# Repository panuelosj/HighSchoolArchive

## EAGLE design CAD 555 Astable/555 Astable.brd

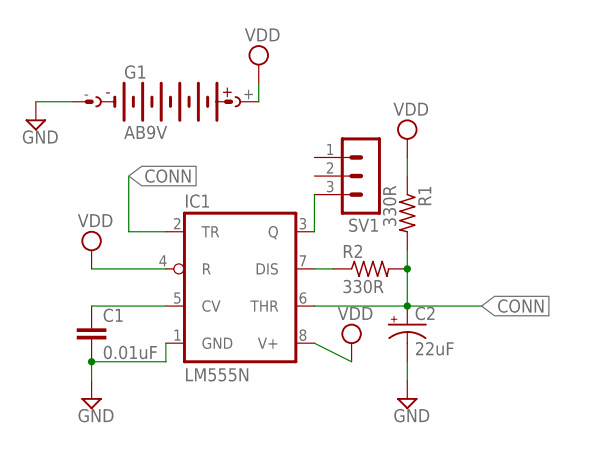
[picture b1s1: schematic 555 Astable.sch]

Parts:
C1: 0.01uF; C5B2.5
C2: 22uF; E3,5-8
G1: AB9V
IC1: LM555N; DIL08
R1, R2: 330R; 0207/10
SV1: MA03-1

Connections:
CONN: C2.+, IC1.2 (TR), IC1.6 (THR), R1.2, R2.2
GND: C1.2, C2.-, G1.-, IC1.1 (GND)
unnamed: C1.1, IC1.5 (CV)
unnamed: IC1.3 (Q), SV1.3
unnamed: IC1.7 (DIS), R2.1
VDD: G1.+, IC1.4 (R), IC1.8 (V+), R1.1

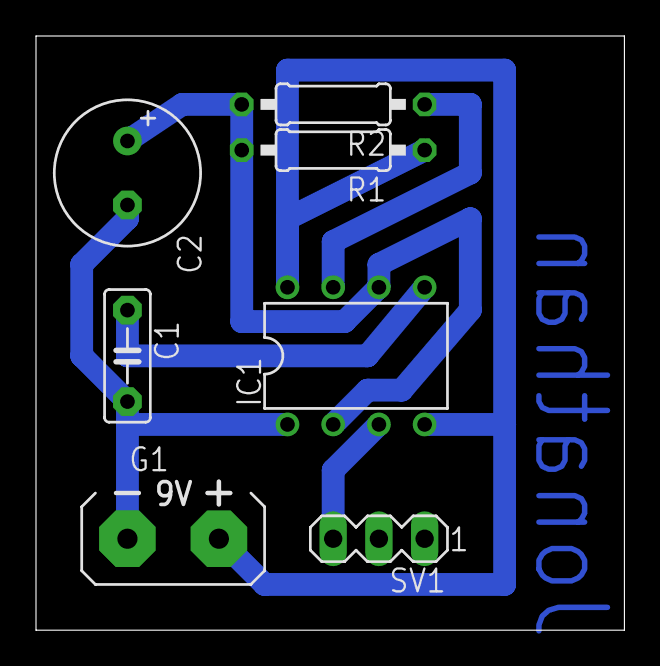
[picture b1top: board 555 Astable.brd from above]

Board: 2 copper layers, 32.7 x 33.0 mm, 7 parts (0 on the bottom side), 6 nets.

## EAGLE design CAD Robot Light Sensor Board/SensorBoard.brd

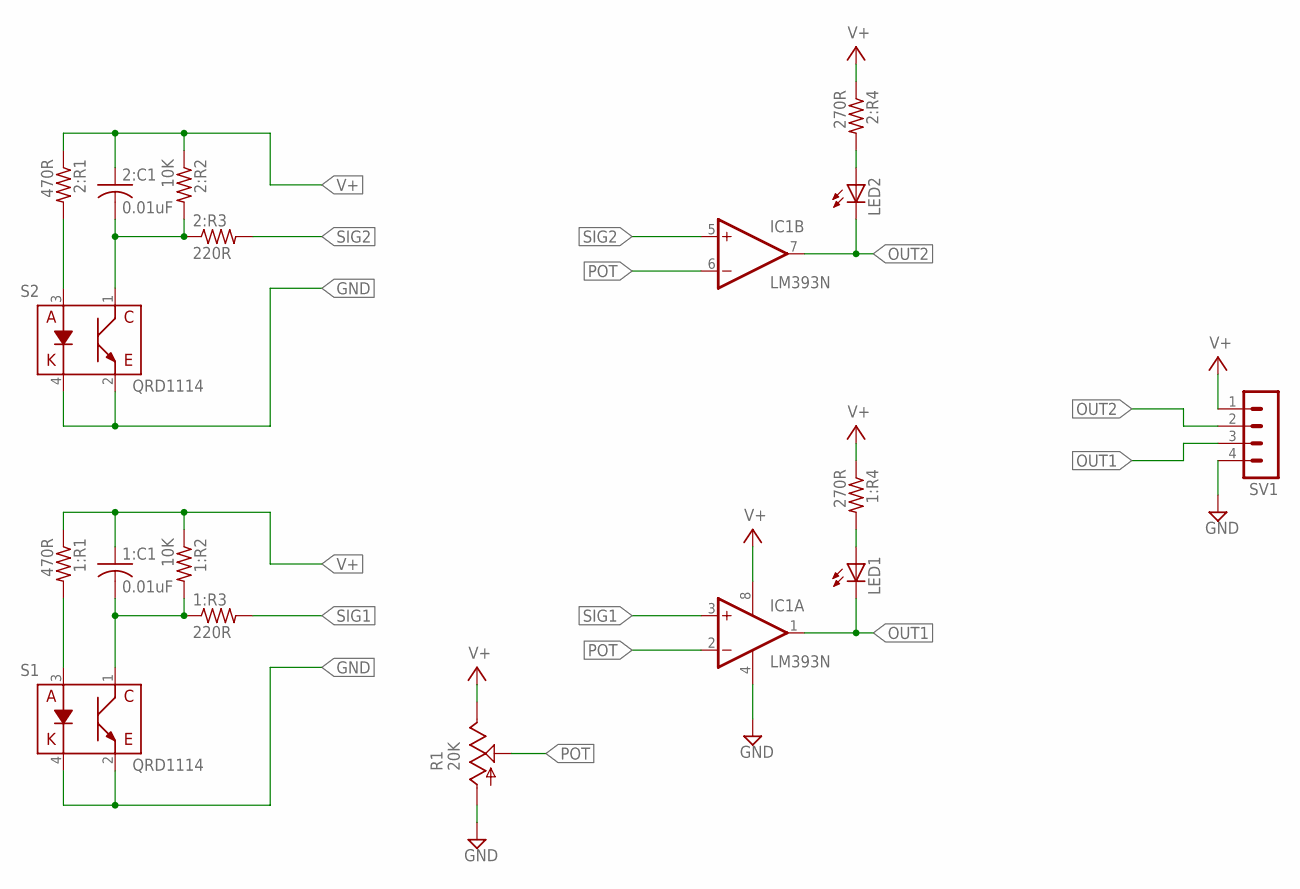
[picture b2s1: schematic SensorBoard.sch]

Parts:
1:C1, 2:C1: 0.01uF; C025-025X050
1:R1, 2:R1: 470R; 0207/12
1:R2, 2:R2: 10K; 0207/12
1:R3, 2:R3: 220R; 0207/10
1:R4, 2:R4: 270R; 0207/12
IC1: LM393N; DIL08
LED1, LED2: LED5MM
R1: 20K; B25P
S1, S2: QRD1114
SV1: MA04-1

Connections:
GND: IC1.4 (V-), R1.A, S1.2 (C), S1.4 (K), S2.2 (C), S2.4 (K), SV1.4
unnamed: 2:R4.2, LED2.A
unnamed: 1:C1.2, 1:R2.2, 1:R3.1, S1.1 (E)
unnamed: 1:R1.2, S1.3 (A)
unnamed: 2:C1.2, 2:R2.2, 2:R3.1, S2.1 (E)
unnamed: 2:R1.2, S2.3 (A)
unnamed: 1:R4.2, LED1.A
OUT1: IC1.1 (OUT), LED1.K (C), SV1.3
OUT2: IC1.7 (OUT), LED2.K (C), SV1.2
POT: IC1.2 (-IN), IC1.6 (-IN), R1.S
SIG1: 1:R3.2, IC1.3 (+IN)
SIG2: 2:R3.2, IC1.5 (+IN)
V+: 1:C1.1, 1:R1.1, 1:R2.1, 1:R4.1, 2:C1.1, 2:R1.1, 2:R2.1, 2:R4.1, IC1.8 (V+), R1.E, SV1.1

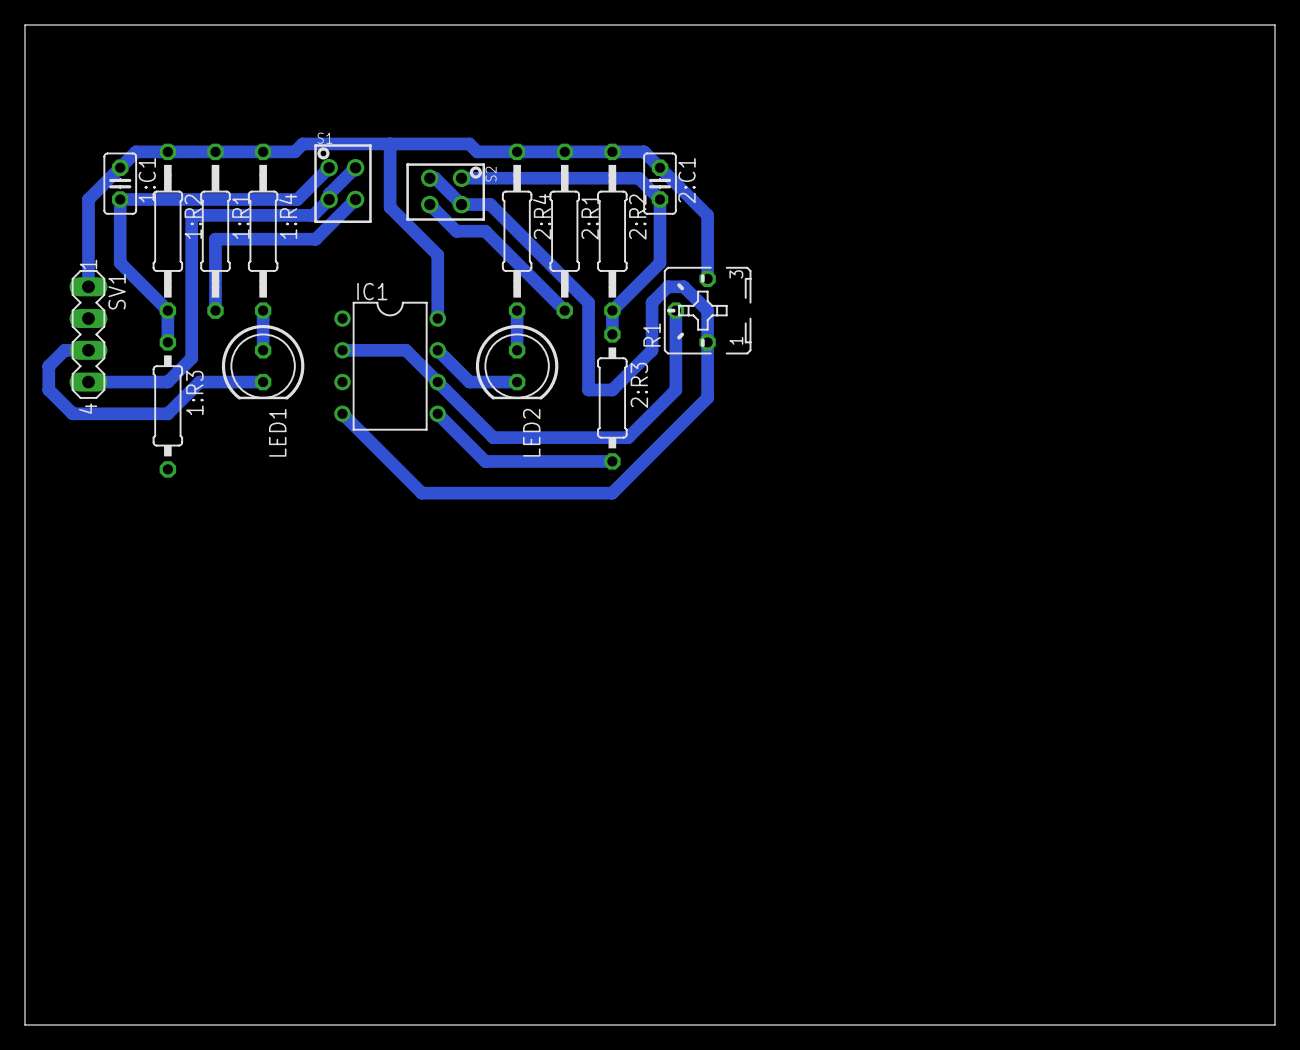
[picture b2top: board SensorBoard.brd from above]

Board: 2 copper layers, 100.0 x 80.0 mm, 17 parts (0 on the bottom side), 13 nets.

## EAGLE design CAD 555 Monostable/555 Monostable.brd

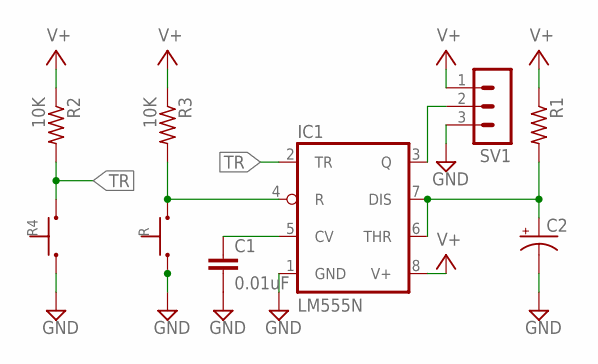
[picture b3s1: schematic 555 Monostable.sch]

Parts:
C1: 0.01uF; C025-025X050
C2: CPOL-USE1.8-4; E1,8-4
IC1: LM555N; DIL08
R, R4: 2PIN
R1: R-US_0207/10; 0207/10
R2, R3: 10K; 0207/10
SV1: MA03-1

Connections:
GND: C1.2, C2.-, IC1.1 (GND), R.1, R4.1, SV1.3
unnamed: IC1.4 (R), R.2, R3.2
unnamed: IC1.3 (Q), SV1.2
unnamed: C1.1, IC1.5 (CV)
unnamed: C2.+, IC1.6 (THR), IC1.7 (DIS), R1.2
TR: IC1.2 (TR), R2.2, R4.2
V+: IC1.8 (V+), R1.1, R2.1, R3.1, SV1.1

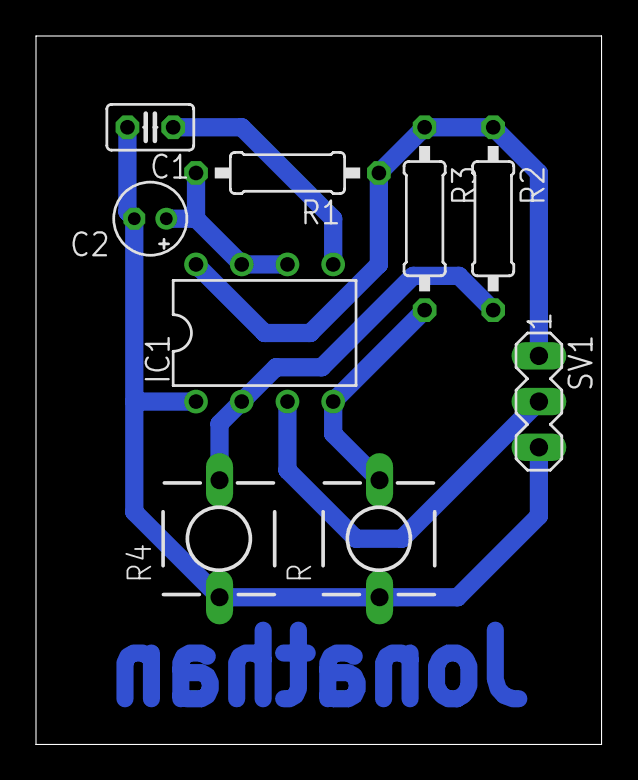
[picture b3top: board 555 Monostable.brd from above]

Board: 2 copper layers, 31.4 x 39.4 mm, 9 parts (0 on the bottom side), 7 nets.

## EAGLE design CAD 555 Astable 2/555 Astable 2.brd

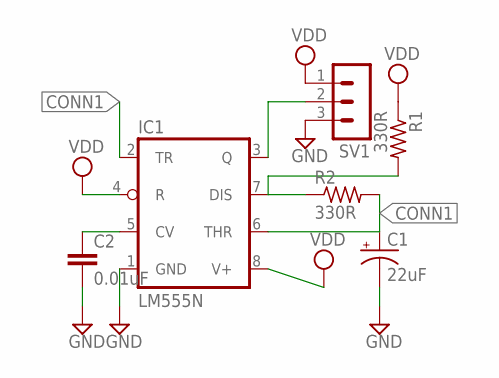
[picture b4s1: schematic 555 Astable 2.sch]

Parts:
C1: 22uF; E1,8-4
C2: 0.01uF; C050-024X044
IC1: LM555N; DIL08
R1, R2: 330R; 0207/10
SV1: MA03-1

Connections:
CONN1: C1.+, IC1.2 (TR), IC1.6 (THR), R2.2
GND: C1.-, C2.2, IC1.1 (GND), SV1.3
unnamed: C2.1, IC1.5 (CV)
unnamed: IC1.7 (DIS), R1.2, R2.1
unnamed: IC1.3 (Q), SV1.2
VDD: IC1.4 (R), IC1.8 (V+), R1.1, SV1.1

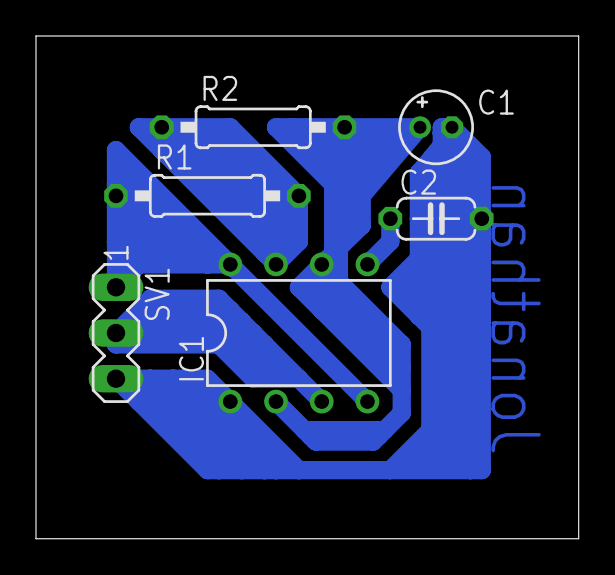
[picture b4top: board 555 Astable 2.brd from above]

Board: 2 copper layers, 30.1 x 27.9 mm, 6 parts (0 on the bottom side), 6 nets.

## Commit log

2017-02-09 Uploaded high school projects to repo as archive
2017-02-09 Added some other CAD boards

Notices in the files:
parts and their libraries:
SparkFun-Sensors: Licensing: Creative Commons ShareAlike 4.0 International - https://creativecommons.org/licenses/by-sa/4.0
